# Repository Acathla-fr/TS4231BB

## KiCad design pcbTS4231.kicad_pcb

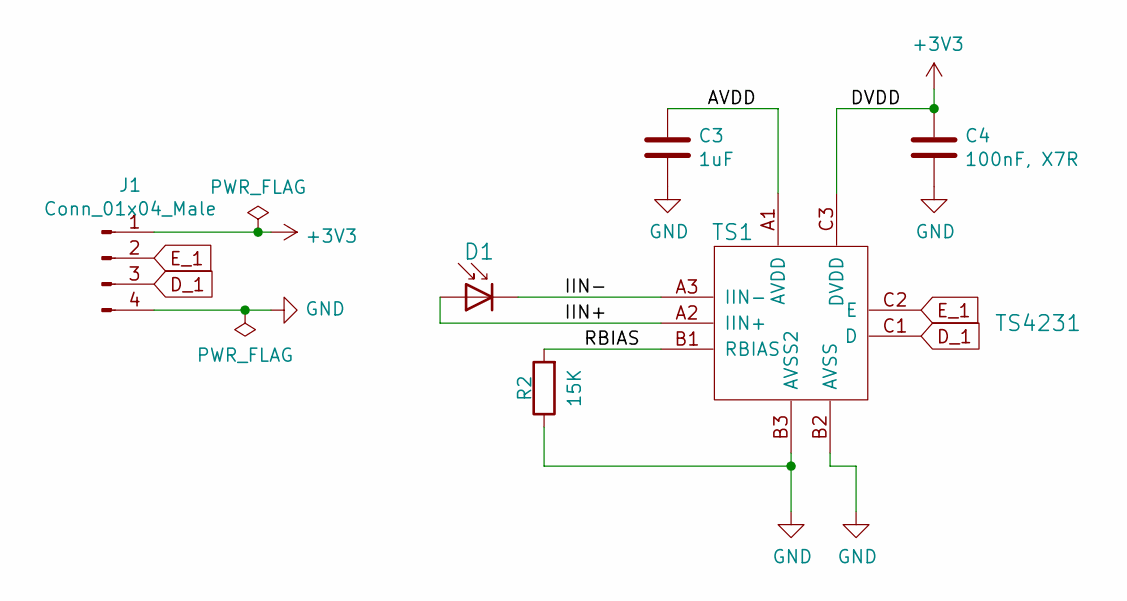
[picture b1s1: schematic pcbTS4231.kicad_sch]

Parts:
C3: 1uF; C_0603_1608Metric
C4: 100nF, X7R; C_0603_1608Metric
D1: VEMD10940F; VEMD10940FX01; MPN VEMD10940F
J1: Conn_01x04_Male; PinHeader_1x04_P2.54mm_Vertical
R2: 15K; R_0603_1608Metric
TS1: TS4231; BGA-9_1.6x1.6mm_Layout3x3_P0.5mm

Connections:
+3V3: C4.1, J1.1, TS1.C3 (DVDD)
/AVDD: C3.1, TS1.A1 (AVDD)
/IIN+: D1.2 (A), TS1.A2 (IIN+)
/IIN-: D1.1 (K), TS1.A3 (IIN-)
/RBIAS: R2.2, TS1.B1 (RBIAS)
D_1: J1.3, TS1.C1 (D)
E_1: J1.2, TS1.C2 (E)
GND: C3.2, C4.2, J1.4, R2.1, TS1.B2 (AVSS), TS1.B3 (AVSS2)

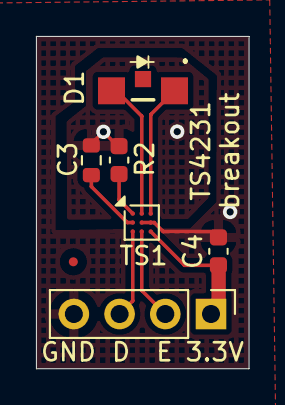
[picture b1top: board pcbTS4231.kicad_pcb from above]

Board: 2 copper layers, 11.8 x 18.5 mm, 6 parts (0 on the bottom side), 8 nets.

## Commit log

2025-02-24 Untested but taken from another working design
